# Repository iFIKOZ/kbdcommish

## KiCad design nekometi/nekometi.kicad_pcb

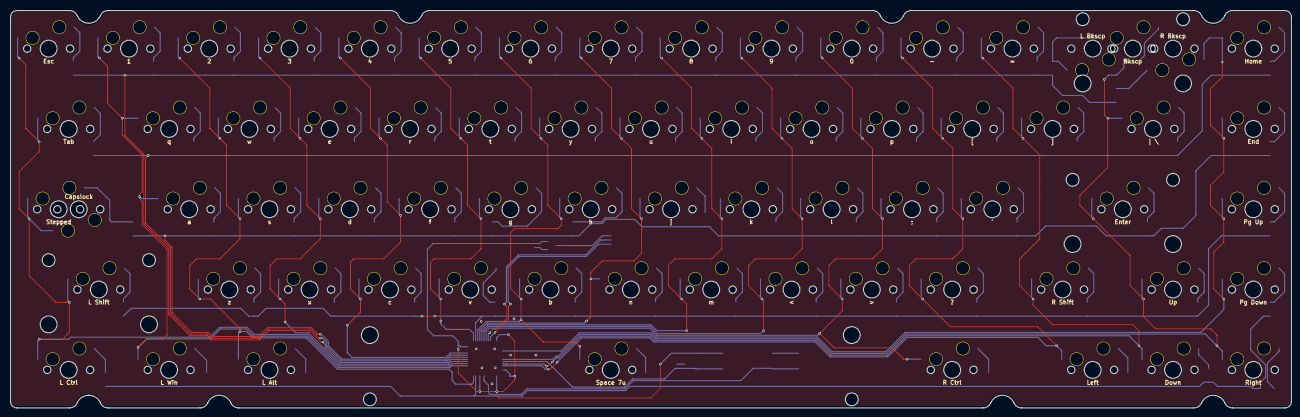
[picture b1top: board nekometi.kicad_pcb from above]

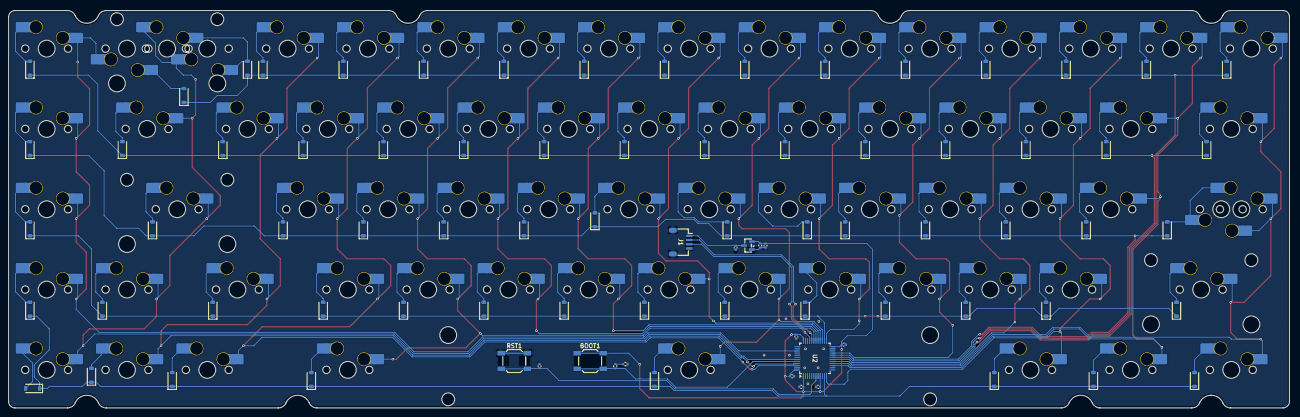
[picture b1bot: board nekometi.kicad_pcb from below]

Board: 2 copper layers, 304.3 x 94.8 mm, 156 parts (83 on the bottom side), 95 nets.

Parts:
BOOT1: BOOT; SW_SPST_SKQG_WithoutStem
C1, C2: 1uF; C_0402_1005Metric
C3: 4.7uF; C_0402_1005Metric
C4, C5, C6, C7, C8, C9: 100nF; C_0402_1005Metric
D1, D2, D3, D4, D5, D6, D7, D8, D9, D10, D11, D12, D13, D14, D15, D16, D17, D18, D19, D20, D21, D22, D23, D24, D25, D26, D27, D28, D29, D30, D31, D32, D33, D34, D35, D36, D37, D38, D39, D40, D41, D42, D43, D44, D45, D46, D47, D48, D49, D50, D51, D52, D53, D54, D55, D56, D57, D58, D59, D60, D61, D62, D63, D64, D65, D66, D67: 1N4148W; D_SOD-123
J1: JST; JST_SH_SM04B-SRSS-TB_1x04-1MP_P1.00mm_Horizontal
R1, R2: 5.1k; R_0402_1005Metric
RST1: RST; SW_SPST_SKQG_WithoutStem
S1: L_Shift; STAB_MX_2u
S2: Enter; STAB_MX_2u
S3: Backspace; STAB_MX_2u
S4: Space; STAB_MX_7u
SW1: Esc; SW_MX_HS_CPG151101S11_1u
SW2: 1; SW_MX_HS_CPG151101S11_1u
SW3: 2; SW_MX_HS_CPG151101S11_1u
SW4: 3; SW_MX_HS_CPG151101S11_1u
SW5: 4; SW_MX_HS_CPG151101S11_1u
SW6: 5; SW_MX_HS_CPG151101S11_1u
SW7: 6; SW_MX_HS_CPG151101S11_1u
SW8: 7; SW_MX_HS_CPG151101S11_1u
SW9: 8; SW_MX_HS_CPG151101S11_1u
SW10: 9; SW_MX_HS_CPG151101S11_1u
SW11: 0; SW_MX_HS_CPG151101S11_1u
SW12: -; SW_MX_HS_CPG151101S11_1u
SW13: =; SW_MX_HS_CPG151101S11_1u
SW14: Bkscp; SW_MX_HS_CPG151101S11_1u
SW15: Home; SW_MX_HS_CPG151101S11_1u
SW16: Tab; SW_MX_HS_CPG151101S11_1.5u
SW17: q; SW_MX_HS_CPG151101S11_1u
SW18: w; SW_MX_HS_CPG151101S11_1u
SW19: e; SW_MX_HS_CPG151101S11_1u
SW20: r; SW_MX_HS_CPG151101S11_1u
SW21: t; SW_MX_HS_CPG151101S11_1u
SW22: y; SW_MX_HS_CPG151101S11_1u
SW23: u; SW_MX_HS_CPG151101S11_1u
SW24: i; SW_MX_HS_CPG151101S11_1u
SW25: o; SW_MX_HS_CPG151101S11_1u
SW26: p; SW_MX_HS_CPG151101S11_1u
SW27: [; SW_MX_HS_CPG151101S11_1u
SW28: ]; SW_MX_HS_CPG151101S11_1u
SW29: | \; SW_MX_HS_CPG151101S11_1u
SW30: End; SW_MX_HS_CPG151101S11_1u
SW31: Capslock; SW_MX_HS_CPG151101S11_1.75u
SW32: a; SW_MX_HS_CPG151101S11_1u
SW33: s; SW_MX_HS_CPG151101S11_1u
SW34: d; SW_MX_HS_CPG151101S11_1u
SW35: f; SW_MX_HS_CPG151101S11_1u
SW36: g; SW_MX_HS_CPG151101S11_1u
SW37: h; SW_MX_HS_CPG151101S11_1u
SW38: j; SW_MX_HS_CPG151101S11_1u
SW39: k; SW_MX_HS_CPG151101S11_1u
SW40: l; SW_MX_HS_CPG151101S11_1u
SW41: ;; SW_MX_HS_CPG151101S11_1u
SW42: '; SW_MX_HS_CPG151101S11_1u
SW43: Enter; SW_MX_HS_CPG151101S11_1u
SW44: Pg Up; SW_MX_HS_CPG151101S11_1u
SW45: L Shift; SW_MX_HS_CPG151101S11_1u
SW46: z; SW_MX_HS_CPG151101S11_1u
SW47: x; SW_MX_HS_CPG151101S11_1u
SW48: c; SW_MX_HS_CPG151101S11_1u
SW49: v; SW_MX_HS_CPG151101S11_1u
SW50: b; SW_MX_HS_CPG151101S11_1u
SW51: n; SW_MX_HS_CPG151101S11_1u
SW52: m; SW_MX_HS_CPG151101S11_1u
SW53: <; SW_MX_HS_CPG151101S11_1u
SW54: >; SW_MX_HS_CPG151101S11_1u
SW55: ?; SW_MX_HS_CPG151101S11_1u
SW56: R Shift; SW_MX_HS_CPG151101S11_1u
SW57: Up; SW_MX_HS_CPG151101S11_1u
SW58: Pg Down; SW_MX_HS_CPG151101S11_1u
SW59: L Ctrl; SW_MX_HS_CPG151101S11_1u
SW60: L Win; SW_MX_HS_CPG151101S11_1u
SW61: L Alt; SW_MX_HS_CPG151101S11_1u
SW62: Space 7u; SW_MX_HS_CPG151101S11_1u
SW63: R Ctrl; SW_MX_HS_CPG151101S11_1u
SW64: Left; SW_MX_HS_CPG151101S11_1u
SW65: Down; SW_MX_HS_CPG151101S11_1u
SW66: Right; SW_MX_HS_CPG151101S11_1u
SW67: Stepped; SW_MX_HS_CPG151101S11_1.75u_STP_1.25
SW68: L Bkscp; SW_MX_HS_CPG151101S11_1u
SW69: R Bkscp; SW_MX_HS_CPG151101S11_1u
U1: XC6206PxxxMR-Regulator_Linear; SOT-23
U2: STM32F072C8Tx; LQFP-48_7x7mm_P0.5mm

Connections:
+3V3: BOOT1.1, C2.2, C3.1, C4.1, C5.1, C6.1, C7.1, C8.1, U1.2 (VO), U2.1 (VBAT), U2.9 (VDDA), U2.24 (VDD), U2.36 (VDDIO2), U2.48 (VDD)
+5V: C1.2, J1.1, U1.3 (VI)
BOOT0: BOOT1.2, R1.1, U2.44 (BOOT0)
Col0: SW1.1, SW16.1, SW31.2, SW45.1, SW59.1, SW67.1, U2.16 (PA6)
Col1: SW2.1, SW17.1, SW32.1, SW60.1, U2.15 (PA5)
Col2: SW3.1, SW18.1, SW33.1, SW46.1, SW61.1, U2.12 (PA2)
Col3: SW4.1, SW19.1, SW34.1, SW47.1, U2.17 (PA7)
Col4: SW5.1, SW20.1, SW35.1, SW48.1, U2.21 (PB10)
Col5: SW6.1, SW21.1, SW36.1, SW49.1, U2.25 (PB12)
Col6: SW7.1, SW22.1, SW37.1, SW50.1, SW62.1, U2.27 (PB14)
Col7: SW8.1, SW23.1, SW38.1, SW51.1, U2.28 (PB15)
Col8: SW9.1, SW24.1, SW39.1, SW52.1, U2.29 (PA8)
Col9: SW10.1, SW25.1, SW40.1, SW53.1, U2.30 (PA9)
Col10: SW11.1, SW26.1, SW41.1, SW54.1, SW63.1, U2.31 (PA10)
Col11: SW12.1, SW27.1, SW42.1, SW55.1, SW64.1, U2.46 (PB9)
Col12: SW13.1, SW28.1, SW56.1, SW65.1, U2.45 (PB8)
Col13: SW14.2, SW29.1, SW43.1, SW57.1, SW66.1, SW68.1, U2.43 (PB7)
Col14: SW15.1, SW30.1, SW44.1, SW58.1, SW69.1, U2.39 (PB3)
D+: J1.3, U2.33 (PA12)
D-: J1.2, U2.32 (PA11)
GND: C1.1, C2.1, C3.2, C4.2, C5.2, C6.2, C7.2, C8.2, C9.1, J1.4, J1.MP (MountPin), R2.2, RST1.1, U1.1 (GND), U2.8 (VSSA), U2.23 (VSS), U2.35 (VSS), U2.47 (VSS)
NRST: C9.2, RST1.2, U2.7 (NRST)
unnamed: D1.2 (A), SW1.2
unnamed: D2.2 (A), SW2.2
unnamed: D3.2 (A), SW3.2
unnamed: D4.2 (A), SW4.2
unnamed: D5.2 (A), SW5.2
unnamed: D6.2 (A), SW6.2
unnamed: D7.2 (A), SW7.2
unnamed: D8.2 (A), SW8.2
unnamed: D9.2 (A), SW9.2
unnamed: D10.2 (A), SW10.2
unnamed: D11.2 (A), SW11.2
unnamed: D12.2 (A), SW12.2
unnamed: D13.2 (A), SW13.2
unnamed: D14.2 (A), SW14.1, SW68.2
unnamed: D15.2 (A), SW15.2
unnamed: D16.2 (A), SW16.2
unnamed: D17.2 (A), SW17.2
unnamed: D18.2 (A), SW18.2
unnamed: D19.2 (A), SW19.2
unnamed: D20.2 (A), SW20.2
unnamed: D21.2 (A), SW21.2
unnamed: D22.2 (A), SW22.2
unnamed: D23.2 (A), SW23.2
unnamed: D24.2 (A), SW24.2
unnamed: D25.2 (A), SW25.2
unnamed: D26.2 (A), SW26.2
unnamed: D27.2 (A), SW27.2
unnamed: D28.2 (A), SW28.2
unnamed: D29.2 (A), SW29.2
unnamed: D30.2 (A), SW30.2
unnamed: D31.2 (A), SW31.1, SW67.2
unnamed: D32.2 (A), SW32.2
unnamed: D33.2 (A), SW33.2
unnamed: D34.2 (A), SW34.2
unnamed: D35.2 (A), SW35.2
unnamed: D36.2 (A), SW36.2
unnamed: D37.2 (A), SW37.2
unnamed: D38.2 (A), SW38.2
unnamed: D39.2 (A), SW39.2
unnamed: D40.2 (A), SW40.2
unnamed: D41.2 (A), SW41.2
unnamed: D42.2 (A), SW42.2
unnamed: D43.2 (A), SW43.2
unnamed: D44.2 (A), SW44.2
unnamed: D45.2 (A), SW45.2
unnamed: D46.2 (A), SW46.2
unnamed: D47.2 (A), SW47.2
unnamed: D48.2 (A), SW48.2
unnamed: D49.2 (A), SW49.2
unnamed: D50.2 (A), SW50.2
unnamed: D51.2 (A), SW51.2
unnamed: D52.2 (A), SW52.2
unnamed: D53.2 (A), SW53.2
unnamed: D54.2 (A), SW54.2
unnamed: D55.2 (A), SW55.2
unnamed: D56.2 (A), SW56.2
unnamed: D57.2 (A), SW57.2
unnamed: D58.2 (A), SW58.2
unnamed: D59.2 (A), SW59.2
unnamed: D60.2 (A), SW60.2
unnamed: D61.2 (A), SW61.2
unnamed: D62.2 (A), SW62.2
unnamed: D63.2 (A), SW63.2
unnamed: D64.2 (A), SW64.2
unnamed: D65.2 (A), SW65.2
unnamed: D66.2 (A), SW66.2
unnamed: D67.2 (A), SW69.2
unnamed: R1.2, R2.1
Row0: D1.1 (K), D2.1 (K), D3.1 (K), D4.1 (K), D5.1 (K), D6.1 (K), D7.1 (K), D8.1 (K), D9.1 (K), D10.1 (K), D11.1 (K), D12.1 (K), D13.1 (K), D14.1 (K), D67.1 (K), U2.18 (PB0)
Row1: D15.1 (K), D16.1 (K), D17.1 (K), D18.1 (K), D19.1 (K), D20.1 (K), D21.1 (K), D22.1 (K), D23.1 (K), D24.1 (K), D25.1 (K), D26.1 (K), D27.1 (K), D28.1 (K), D29.1 (K), U2.19 (PB1)
Row2: D30.1 (K), D31.1 (K), D32.1 (K), D33.1 (K), D34.1 (K), D35.1 (K), D36.1 (K), D37.1 (K), D38.1 (K), D39.1 (K), D40.1 (K), D41.1 (K), D42.1 (K), D43.1 (K), U2.20 (PB2)
Row3: D44.1 (K), D45.1 (K), D46.1 (K), D47.1 (K), D48.1 (K), D49.1 (K), D50.1 (K), D51.1 (K), D52.1 (K), D53.1 (K), D54.1 (K), D55.1 (K), D56.1 (K), D57.1 (K), U2.26 (PB13)
Row4: D58.1 (K), D59.1 (K), D60.1 (K), D61.1 (K), D62.1 (K), D63.1 (K), D64.1 (K), D65.1 (K), D66.1 (K), U2.11 (PA1)
